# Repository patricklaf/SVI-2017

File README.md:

# SVI-2017

English - [Français](LISEZMOI.md)

The SVI-2017 board is the recreation of the interface board for the RobotArm SVI 2000.

The functional board in version 1.1 is compatible with MSX computers.

## KiCad Project

The original project dates from 2017.

The [KiCad](KiCad/) folder contains the project migrated to KiCad 8.0.4.

The original archive [SVI-2017-201711091030.zip](https://github.com/patricklaf/SVI-2017/raw/main/KiCad/Gerber/SVI-2017-201711091030.zip) contains the Gerber files needed to produce the PCB. The build has been successfully tested by [Seeedstudio](https://www.seeedstudio.com/fusion_pcb.html).

An [interactive BOM](https://patricklaf.github.io/SVI-2017/bom.html) is available to view the list of required components and help with assembly.

You can order PCB directly from shared project on PCBWay.

## ROM

The [ROGO.ROM](https://github.com/patricklaf/SVI-2017/raw/main/ROM/ROGO.ROM) file is the image needed to program the EEPROM of the board.

The file combines the following elements:

- The ROGO ROM for MSX.
- The modified ROGO ROM for MSX 2, MSX 2+ and MSX TurboR.

## Usage

The DIP switch on the board selects the operating mode of the board.

Switch 1 selects the ROGO ROM or PIO mode.

Switch 2 selects the model of the computer used to activate the compatible ROM.

## ROGO

The ROGO language, similar to the Logo language, allows the robot to be controlled using commands.

A drawing of the robot on the screen reproduces the movements made.

## PIO

In PIO mode, the robot's movements are made by directly activating the motors, in one direction or another. Ports 0 and 1 are used. A movement is activated by setting the corresponding bit to 1. The movement stops when the bit is set to 0.

Port 0

| Bit | Movement               |
|:---:|:-----------------------|
| 0   | Axis 2, arm forward    |
| 1   | Axis 2, arm back       |
| 2   | Axis 1, left rotation  |
| 3   | Axis 1, right rotation |
| 4   | Axis 5, clamp closing  |
| 5   | Axis 5, clamp opening  |

Port 1

| Bit | Movement                     |
|:---:|:-----------------------------|
| 0   | Axis 3, arm down             |
| 1   | Axis 3, arm up               |
| 2   | Axis 1, clamp rotation left  |
| 3   | Axis 1, clamp rotation right |

> [!CAUTION]
> Never activate the 2 movements of an axis simultaneously, otherwise you risk damaging the electronics of the card.

## Acknowledgments

This project could not have been completed without the invaluable help of the members of the [MSX Village](https://msxvillage.fr) website.

There is a dedicated topic on the site's forum: [Robotarm SVI the diagram](https://msxvillage.fr/forum/topic-326-1+robotarm-svi-le-schema.php).

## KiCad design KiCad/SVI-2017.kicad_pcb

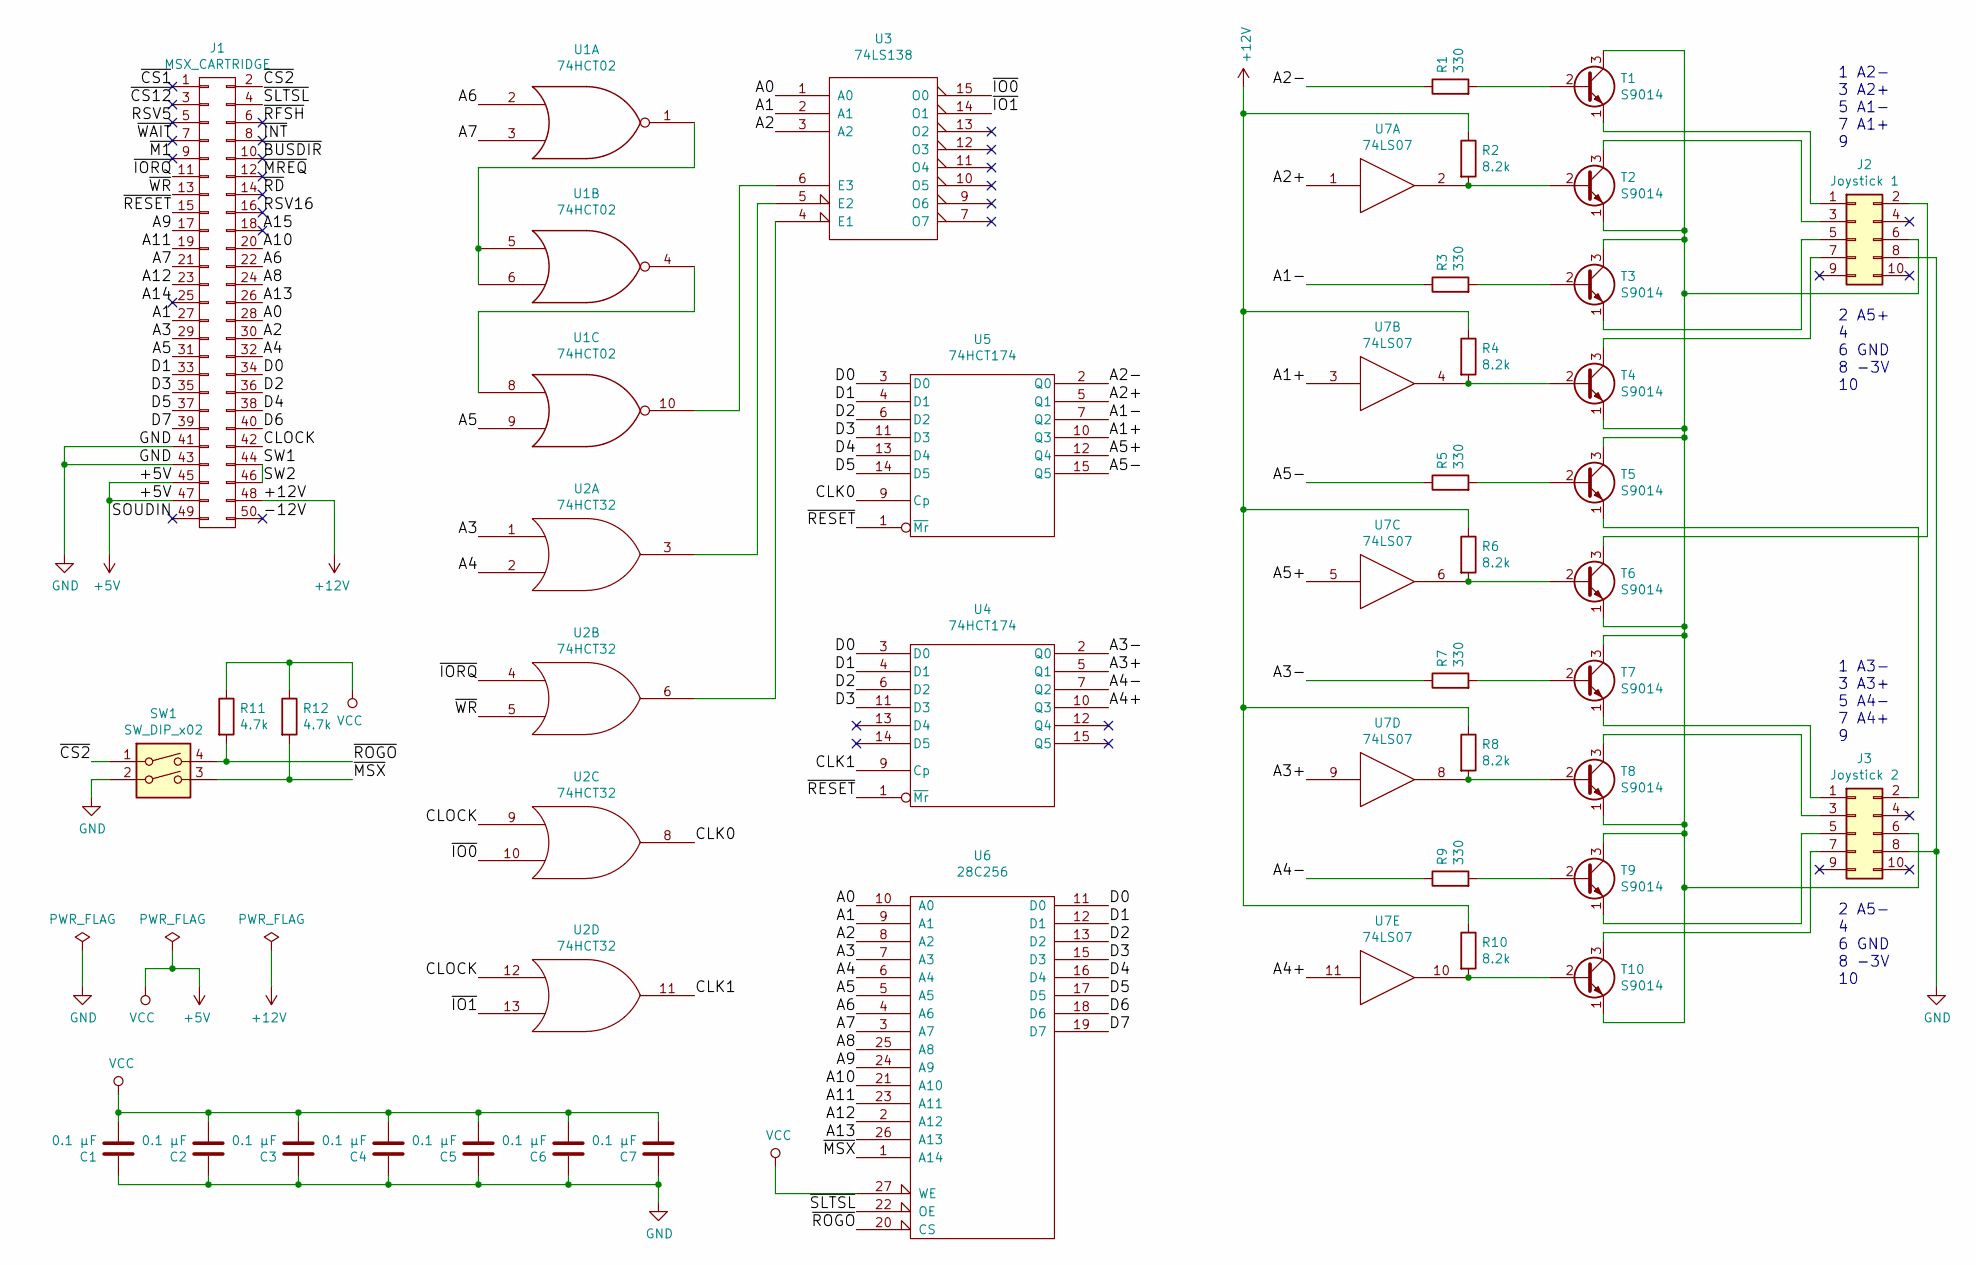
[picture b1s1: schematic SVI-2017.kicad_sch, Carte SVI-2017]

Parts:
C1, C2, C3, C4, C5, C6, C7: 0.1 µF; C_Disc_D5.1mm_W3.2mm_P5.00mm
J1: MSX_CARTRIDGE
J2: Joystick 1; IDC-Header_2x05_Pitch2.54mm_Straight
J3: Joystick 2; IDC-Header_2x05_Pitch2.54mm_Straight
R1, R3, R5, R7, R9: 330; R_Axial_DIN0207_L6.3mm_D2.5mm_P10.16mm_Horizontal
R2, R4, R6, R8, R10: 8.2k; R_Axial_DIN0207_L6.3mm_D2.5mm_P10.16mm_Horizontal
R11, R12: 4.7k; R_Axial_DIN0207_L6.3mm_D2.5mm_P10.16mm_Horizontal
SW1: SW_DIP_x02; SW_DIP_x2_W7.62mm_Slide
T1, T2, T3, T4, T5, T6, T7, T8, T9, T10: S9014; TO-92_Inline_Narrow_Oval
U1: 74HCT02; DIP-14_W7.62mm_Socket
U2: 74HCT32; DIP-14_W7.62mm_Socket
U3: 74LS138; DIP-16_W7.62mm_Socket
U4, U5: 74HCT174; DIP-16_W7.62mm_Socket
U6: 28C256; DIP-28_W15.24mm_Socket
U7: 74LS07; DIP-14_W7.62mm_Socket

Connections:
+5V: C1.2, C2.2, C3.2, C4.2, C5.2, C6.2, C7.2, J1.45, J1.47, R11.1, R12.1, U1.14 (VCC), U2.14 (VCC), U3.16 (VCC), U4.16 (VCC), U5.16 (VCC), U6.27 (WE), U6.28 (VCC), U7.14 (VCC)
+12V: J1.48, R2.1, R4.1, R6.1, R8.1, R10.1
/-12V: J1.50
/A0: J1.28, U3.1 (A0), U6.10 (A0)
/A1: J1.27, U3.2 (A1), U6.9 (A1)
/A1+: U5.10 (Q3), U7.3
/A1-: R3.1, U5.7 (Q2)
/A2: J1.30, U3.3 (A2), U6.8 (A2)
/A2+: U5.5 (Q1), U7.1
/A2-: R1.1, U5.2 (Q0)
/A3: J1.29, U2.1, U6.7 (A3)
/A3+: U4.5 (Q1), U7.9
/A3-: R7.1, U4.2 (Q0)
/A4: J1.32, U2.2, U6.6 (A4)
/A4+: U4.10 (Q3), U7.11
/A4-: R9.1, U4.7 (Q2)
/A5: J1.31, U1.9, U6.5 (A5)
/A5+: U5.12 (Q4), U7.5
/A5-: R5.1, U5.15 (Q5)
/A6: J1.22, U1.2, U6.4 (A6)
/A7: J1.21, U1.3, U6.3 (A7)
/A8: J1.24, U6.25 (A8)
/A9: J1.17, U6.24 (A9)
/A10: J1.20, U6.21 (A10)
/A11: J1.19, U6.23 (A11)
/A12: J1.23, U6.2 (A12)
/A13: J1.26, U6.26 (A13)
/A14: J1.25
/A15: J1.18
/CLK0: U2.8, U5.9 (Cp)
/CLK1: U2.11, U4.9 (Cp)
/CLOCK: J1.42, U2.9, U2.12
/D0: J1.34, U4.3 (D0), U5.3 (D0), U6.11 (D0)
/D1: J1.33, U4.4 (D1), U5.4 (D1), U6.12 (D1)
/D2: J1.36, U4.6 (D2), U5.6 (D2), U6.13 (D2)
/D3: J1.35, U4.11 (D3), U5.11 (D3), U6.15 (D3)
/D4: J1.38, U5.13 (D4), U6.16 (D4)
/D5: J1.37, U5.14 (D5), U6.17 (D5)
/D6: J1.40, U6.18 (D6)
/D7: J1.39, U6.19 (D7)
/RSV5: J1.5
/RSV16: J1.16
/SW1: J1.44, J1.46
/~BUSDIR: J1.10
/~CS1: J1.1
/~CS2: J1.2, SW1.1
/~CS12: J1.3
/~INT: J1.8
/~IO0: U2.10, U3.15 (O0)
/~IO1: U2.13, U3.14 (O1)
/~IORQ: J1.11, U2.4
/~M1: J1.9
/~MREQ: J1.12
/~MSX: R12.2, SW1.3, U6.1 (A14)
/~RD: J1.14
/~RESET: J1.15, U4.1 (~Mr), U5.1 (~Mr)
/~RFSH: J1.6
/~ROGO: R11.2, SW1.4, U6.20 (CS)
/~SLTSL: J1.4, U6.22 (OE)
/~WAIT: J1.7
/~WR: J1.13, U2.5
GND: C1.1, C2.1, C3.1, C4.1, C5.1, C6.1, C7.1, J1.41, J1.43, J2.8, J3.8, SW1.2, U1.7 (GND), U2.7 (GND), U3.8 (GND), U4.8 (GND), U5.8 (GND), U6.14 (GND), U7.7 (GND); also elsewhere on the board
unnamed: J2.1, T1.1 (E)
unnamed: J2.2, T6.3 (C)
unnamed: J2.3, T2.3 (C)
unnamed: J2.5, T3.1 (E)
unnamed: J2.6, J3.6, T1.3 (C), T2.1 (E), T3.3 (C), T4.1 (E), T5.3 (C), T6.1 (E), T7.3 (C), T8.1 (E), T9.3 (C), T10.1 (E)
unnamed: J2.7, T4.3 (C)
unnamed: J3.1, T7.1 (E)
unnamed: J3.2, T5.1 (E)
unnamed: J3.3, T8.3 (C)
unnamed: J3.5, T9.1 (E)
unnamed: J3.7, T10.3 (C)
unnamed: R1.2, T1.2 (B)
unnamed: R2.2, T2.2 (B), U7.2
unnamed: R3.2, T3.2 (B)
unnamed: R4.2, T4.2 (B), U7.4
unnamed: R5.2, T5.2 (B)
unnamed: R6.2, T6.2 (B), U7.6
unnamed: R7.2, T7.2 (B)
unnamed: R8.2, T8.2 (B), U7.8
unnamed: R9.2, T9.2 (B)
unnamed: R10.2, T10.2 (B), U7.10
unnamed: U1.1, U1.5, U1.6
unnamed: U1.4, U1.8
unnamed: U1.10, U3.6 (E3)
unnamed: U2.3, U3.5 (E2)
unnamed: U2.6, U3.4 (E1)

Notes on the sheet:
2 A5- 4 6 GND 8 -3V 10
1 A2- 3 A2+ 5 A1- 7 A1+ 9
1 A3- 3 A3+ 5 A4- 7 A4+ 9
2 A5+ 4 6 GND 8 -3V 10

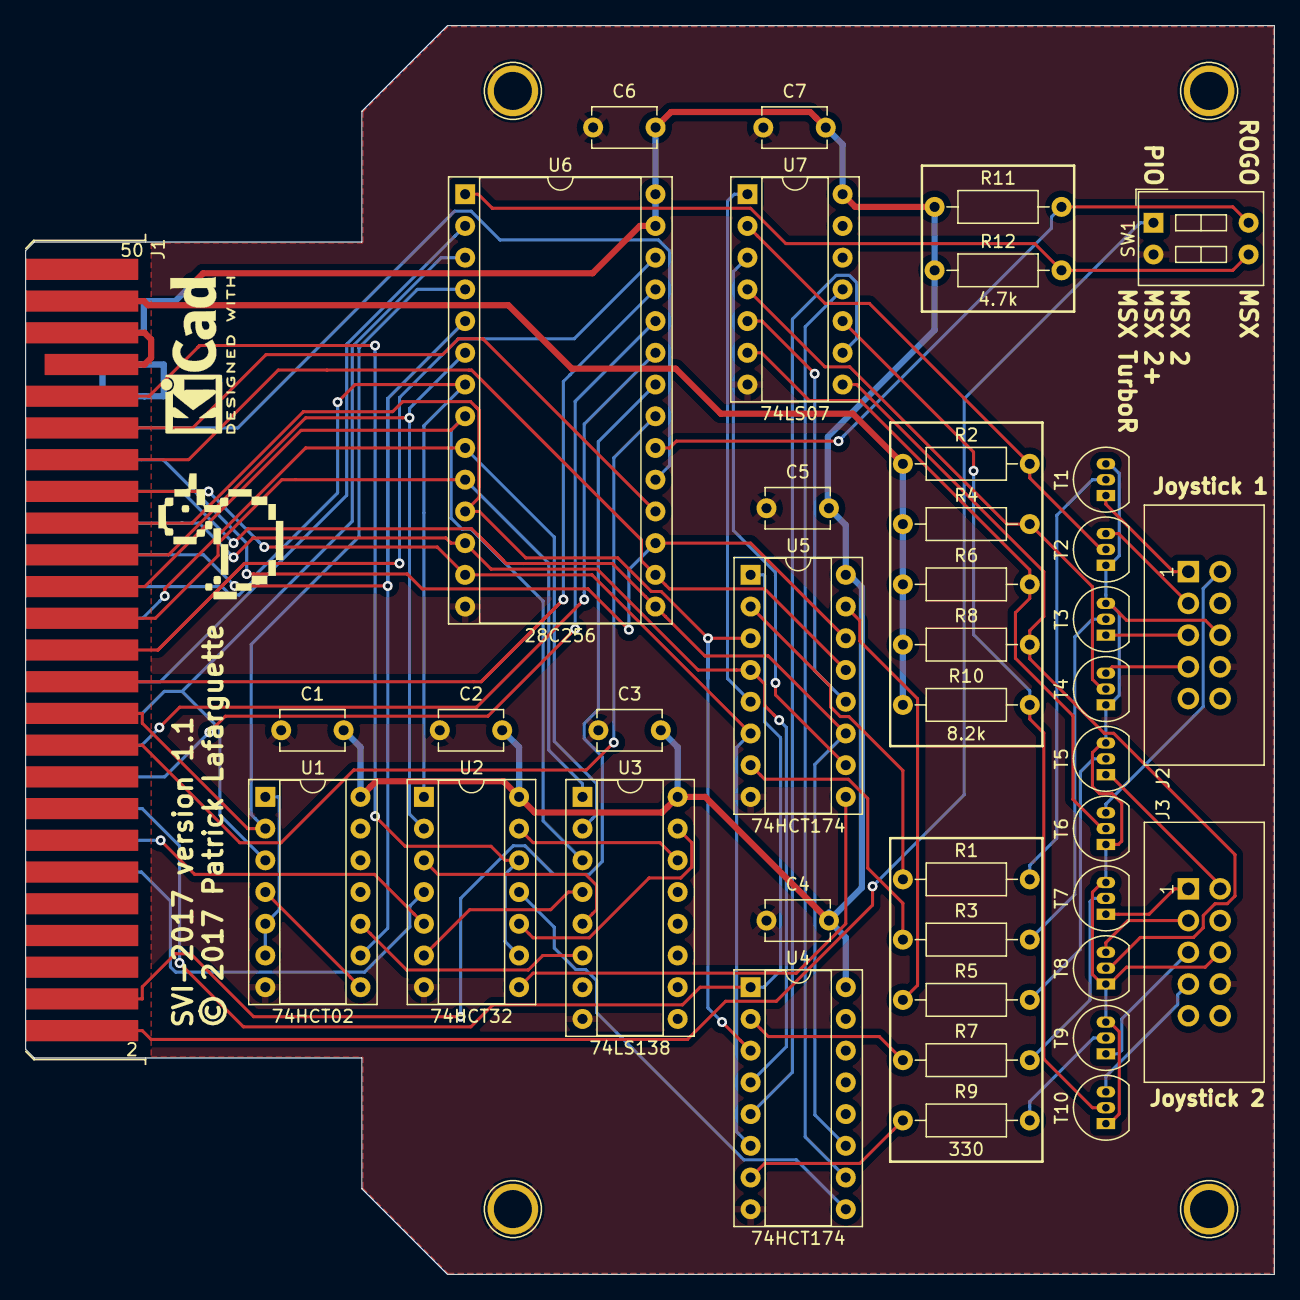
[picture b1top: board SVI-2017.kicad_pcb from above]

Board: 2 copper layers, 100.0 x 100.0 mm, 46 parts (0 on the bottom side), 74 nets.

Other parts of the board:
BL: 1pin
BR: 1pin
COINCOIN: LOGO; COINCOIN
KICAD: KiCad-Logo2_12mm_SilkScreen; KiCad-Logo2_6mm_SilkScreen
TL: 1pin
TR: 1pin

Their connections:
GND: BL.1, BR.1, TL.1, TR.1; also elsewhere on the board

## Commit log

2024-07-27 Ajout du projet KiCad
2024-07-27 Ajout du fichier README.md
2024-07-29 Modification du fichier README.
    - Ajout d'une photographie.
    - Ajout du fichier ROM.
    - Ajout des sections ROM, utilisation, ROGO et PIO.
2024-08-19 Correction d'un nom de fichier
2024-08-19 Passage de README.md en langue anglaise et ajout de LISEZMOI.md toujours en français
2024-08-19 Correction du lien vers la ROM pour permettre le téléchargement direct
2024-08-19 Ajout du lien vers PCBWay

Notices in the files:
KiCad/SVI-2017.kicad_pcb:
© 2017 Patrick Lafarguette
KiCad/SVI-2017.kicad_sch:
© 2017-2024 Patrick Lafarguette
